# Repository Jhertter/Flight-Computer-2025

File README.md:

# ITBA Rocketry Team - Avionics&recovery
Documentation of SRAD Flight Computer

---

## Description

- Hardware design and implementation of the 2025 on board flight computer.
- Software used to capture data and transmit it to the ground station.

## FC implementation diagram

## Authors

José Ivan Hertter
Ezequiel Diaz Guzmán

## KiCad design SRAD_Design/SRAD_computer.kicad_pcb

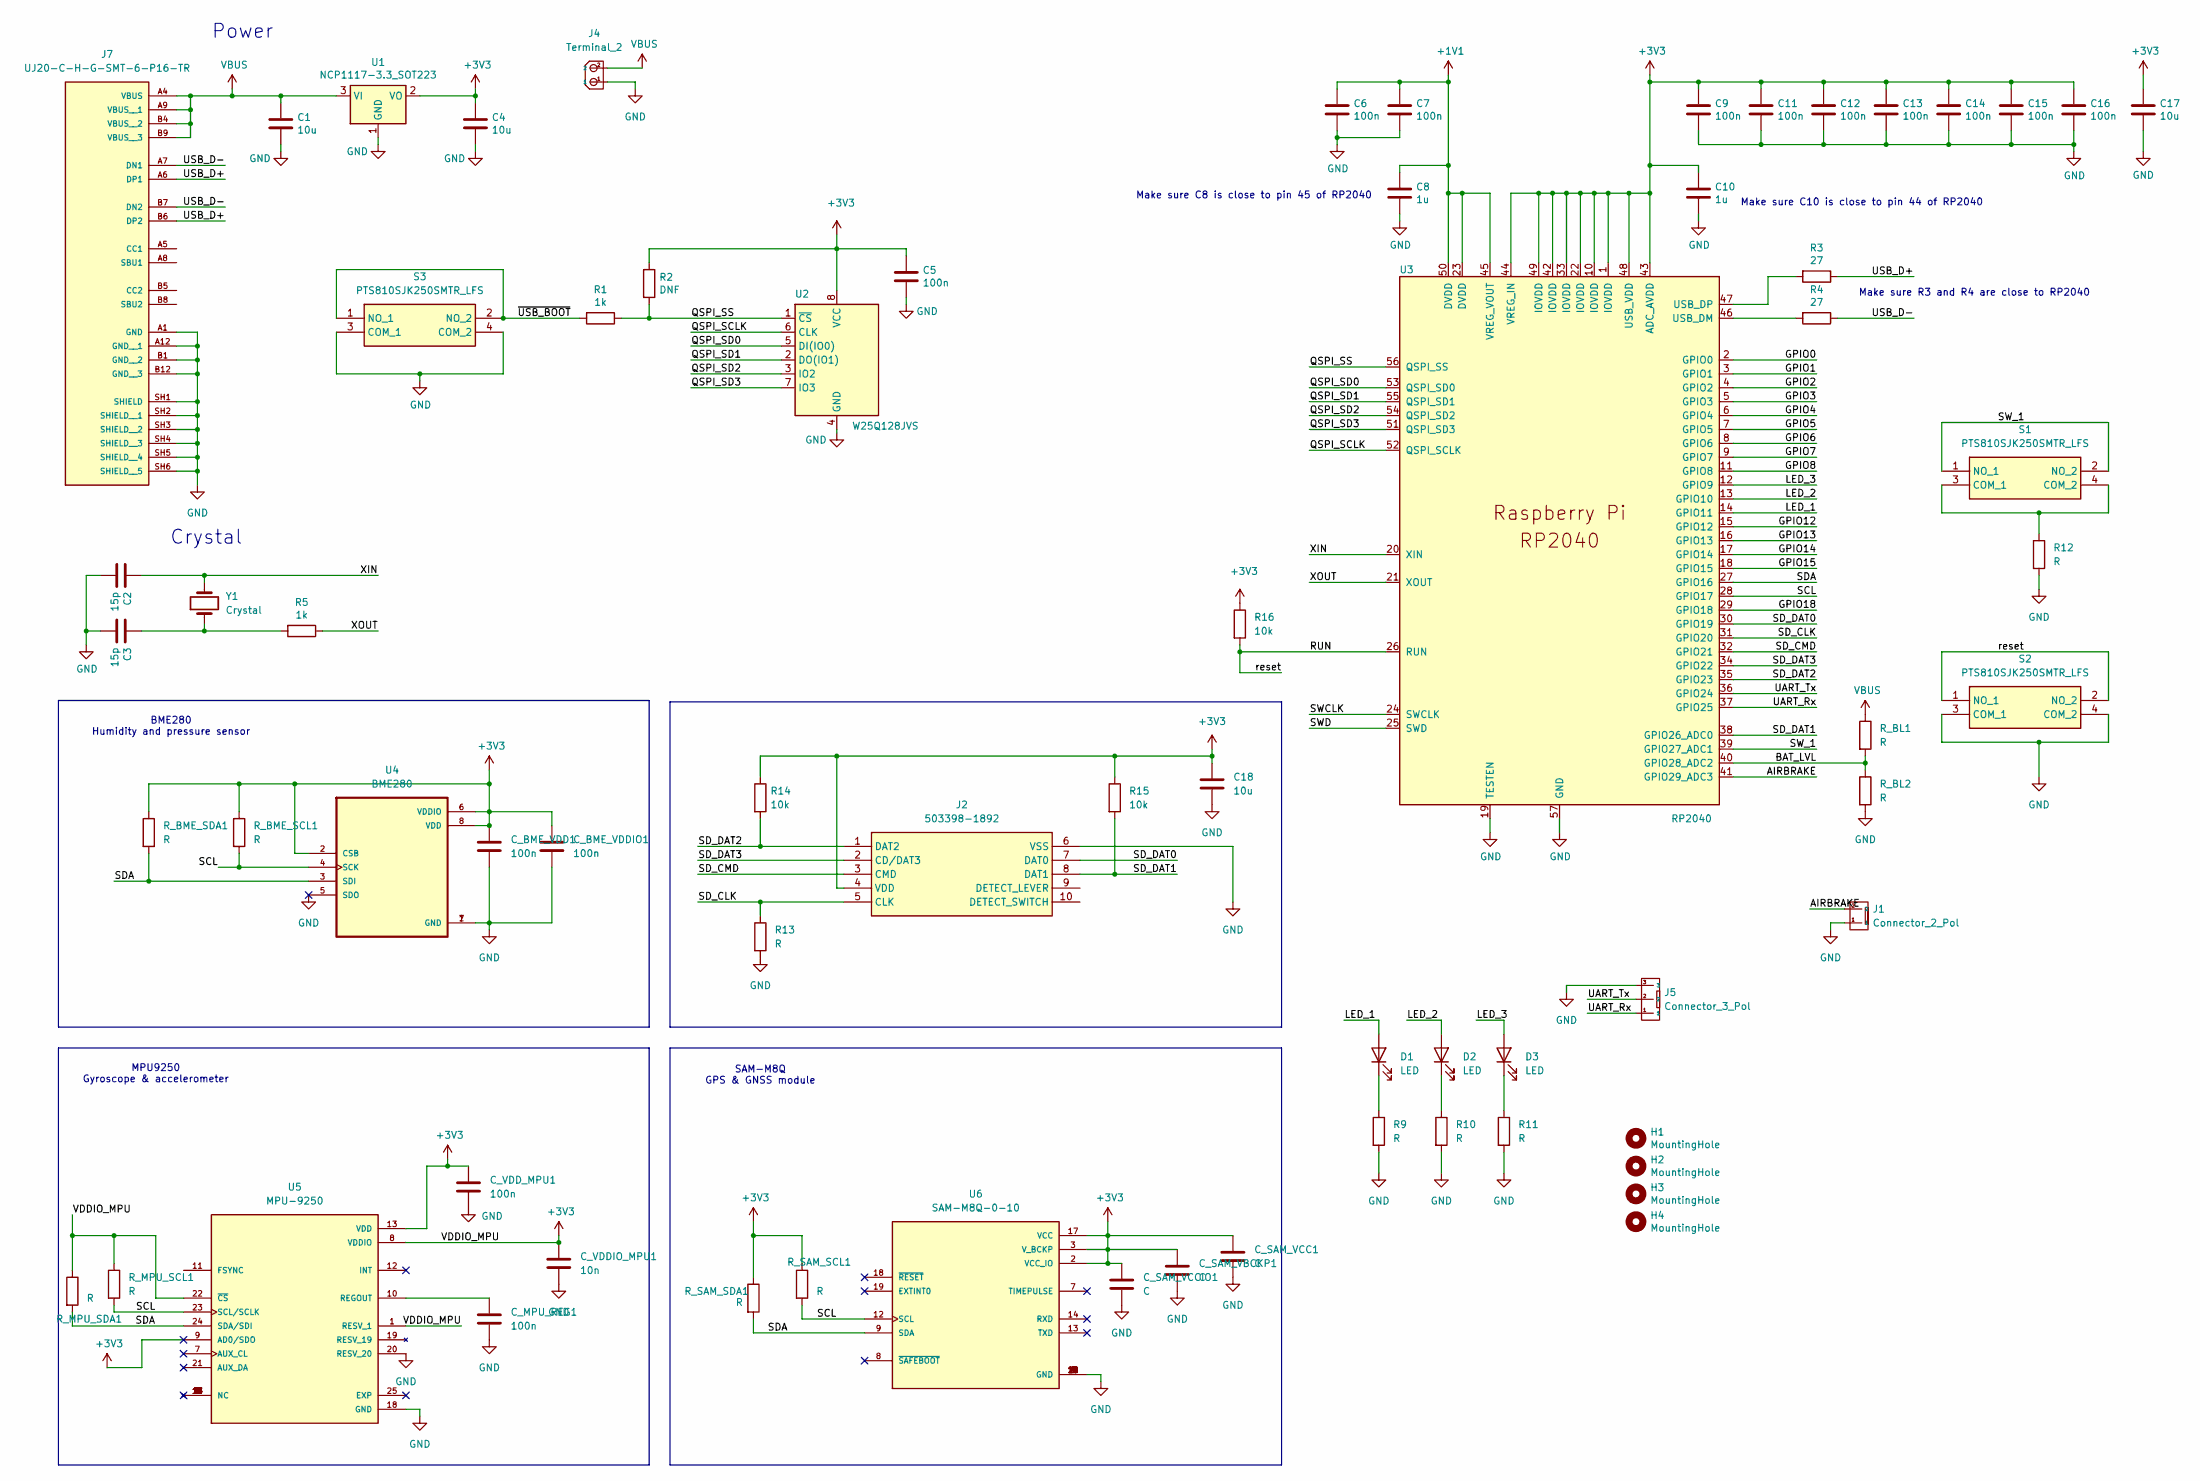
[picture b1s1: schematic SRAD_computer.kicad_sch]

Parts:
C1, C4, C17: 10u; C_0805_2012Metric
C2, C3: 15p; C_0805_2012Metric
C5, C6, C7, C9, C11, C12, C13, C14, C15, C16: 100n; C_0805_2012Metric
C8, C10: 1u; C_0805_2012Metric
C18: 10u; C_0805
C_BME_VDD1: 100n; C_0805
C_BME_VDDIO1: 100n; C_0805
C_MPU_REG1: 100n; C_0805
C_SAM_VBCKP1: C; C_0805
C_SAM_VCC1: C; C_0805
C_SAM_VCCIO1: C; C_0805
C_VDDIO_MPU1: 10n; C_0805
C_VDD_MPU1: 100n; C_0805
D1, D2, D3: LED; LED_0805_2012Metric_Pad1.15x1.40mm_HandSolder
H1, H2, H3, H4: MountingHole; MountingHole_3.5mm
J1: Connector_2_Pol; PinHeader_1x02_P2.54mm_Vertical
J2: 503398-1892; 693071010811; Mouser Part Number 538-503398-1892
J4: Terminal_2; Bornera_2_P5mm
J5: Connector_3_Pol; PinHeader_1x03_P2.54mm_Vertical
J7: UJ20-C-H-G-SMT-6-P16-TR; SAMESKY_UJ20-C-H-G-SMT-6-P16-TR; PARTREV 1.01
R1, R5: 1k; R_0805_2012Metric
R2: DNF; R_0805_2012Metric
R3, R4: 27; R_0805_2012Metric
R9: R; R_0805_2012Metric_Pad1.20x1.40mm_HandSolder
R10, R11, R12, R13: R; R_0805
R14, R15, R16: 10k; R_0805
R_BL1, R_BL2: R; R_0805
R_BME_SCL1: R; R_0805
R_BME_SDA1: R; R_0805
R_MPU_SCL1: R; R_0805
R_MPU_SDA1: R; R_0805
R_SAM_SCL1: R; R_0805
R_SAM_SDA1: R; R_0805
S1, S2, S3: PTS810SJK250SMTR_LFS; PTS810SJK250SMTRLFS; Mouser Part Number 611-PTS810SJK250SMTR
U1: NCP1117-3.3_SOT223; SOT-223-3_TabPin2
U2: W25Q128JVS; SOIC-8_5.3x5.3mm_P1.27mm
U3: RP2040; RP2040-QFN-56
U4: BME280; PSON65P250X250X100-8N
U5: MPU-9250; PARTREV 1.1
U6: SAM-M8Q-0-10; MODULE_SAM-M8Q-0-10; PARTREV R07
Y1: Crystal; Crystal_HC49-4H_Vertical

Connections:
+1V1: C6.1, C7.1, C8.1, U3.23 (DVDD), U3.45 (VREG_VOUT), U3.50 (DVDD)
+3V3: C4.1, C5.1, C9.1, C10.1, C11.1, C12.1, C13.1, C14.1, C15.1, C16.1, C17.1, C18.1, C_BME_VDD1.1, C_BME_VDDIO1.1, C_SAM_VBCKP1.1, C_SAM_VCC1.1, C_SAM_VCCIO1.1, C_VDDIO_MPU1.1, C_VDD_MPU1.1, J2.4 (VDD), R2.1, R14.1, R15.1, R16.1, R_BME_SCL1.1, R_BME_SDA1.1, R_MPU_SCL1.1, R_MPU_SDA1.1, R_SAM_SCL1.1, R_SAM_SDA1.1, U1.2 (VO), U2.8 (VCC), U3.1 (IOVDD), U3.10 (IOVDD), U3.22 (IOVDD), U3.33 (IOVDD), U3.42 (IOVDD), U3.43 (ADC_AVDD), U3.44 (VREG_IN), U3.48 (USB_VDD), U3.49 (IOVDD), U4.2 (CSB), U4.6 (VDDIO), U4.8 (VDD), U5.1 (RESV_1), U5.8 (VDDIO), U5.9 (AD0/SDO), U5.13 (VDD), U5.22 (~CS), U6.2 (VCC_IO), U6.3 (V_BCKP), U6.17 (VCC)
/AIRBRAKE: J1.2, U3.41 (GPIO29_ADC3)
/BAT_LVL: R_BL1.2, R_BL2.1, U3.40 (GPIO28_ADC2)
/GPIO0: U3.2 (GPIO0)
/GPIO1: U3.3 (GPIO1)
/GPIO2: U3.4 (GPIO2)
/GPIO3: U3.5 (GPIO3)
/GPIO4: U3.6 (GPIO4)
/GPIO5: U3.7 (GPIO5)
/GPIO6: U3.8 (GPIO6)
/GPIO7: U3.9 (GPIO7)
/GPIO8: U3.11 (GPIO8)
/GPIO12: U3.15 (GPIO12)
/GPIO13: U3.16 (GPIO13)
/GPIO14: U3.17 (GPIO14)
/GPIO15: U3.18 (GPIO15)
/GPIO18: U3.29 (GPIO18)
/LED_1: D1.2 (A), U3.14 (GPIO11)
/LED_2: D2.2 (A), U3.13 (GPIO10)
/LED_3: D3.2 (A), U3.12 (GPIO9)
/QSPI_SCLK: U2.6 (CLK), U3.52 (QSPI_SCLK)
/QSPI_SD0: U2.5 (DI(IO0)), U3.53 (QSPI_SD0)
/QSPI_SD1: U2.2 (DO(IO1)), U3.55 (QSPI_SD1)
/QSPI_SD2: U2.3 (IO2), U3.54 (QSPI_SD2)
/QSPI_SD3: U2.7 (IO3), U3.51 (QSPI_SD3)
/QSPI_SS: R1.1, R2.2, U2.1 (~CS), U3.56 (QSPI_SS)
/RUN: R16.2, S2.1 (NO_1), S2.2 (NO_2), U3.26 (RUN)
/SCL: R_BME_SCL1.2, R_MPU_SCL1.2, R_SAM_SCL1.2, U3.28 (GPIO17), U4.4 (SCK), U5.23 (SCL/SCLK), U6.12 (SCL)
/SDA: R_BME_SDA1.2, R_MPU_SDA1.2, R_SAM_SDA1.2, U3.27 (GPIO16), U4.3 (SDI), U5.24 (SDA/SDI), U6.9 (SDA)
/SD_CLK: J2.5 (CLK), R13.1, U3.31 (GPIO20)
/SD_CMD: J2.3 (CMD), U3.32 (GPIO21)
/SD_DAT0: J2.7 (DAT0), U3.30 (GPIO19)
/SD_DAT1: J2.8 (DAT1), R15.2, U3.38 (GPIO26_ADC0)
/SD_DAT2: J2.1 (DAT2), R14.2, U3.35 (GPIO23)
/SD_DAT3: J2.2 (CD/DAT3), U3.34 (GPIO22)
/SWCLK: U3.24 (SWCLK)
/SWD: U3.25 (SWD)
/SW_1: S1.1 (NO_1), S1.2 (NO_2), U3.39 (GPIO27_ADC1)
/UART_Rx: J5.1, U3.37 (GPIO25)
/UART_Tx: J5.2, U3.36 (GPIO24)
/USB_D+: J7.A6 (DP1), J7.B6 (DP2), R3.1
/USB_D-: J7.A7 (DN1), J7.B7 (DN2), R4.1
/XIN: C2.1, U3.20 (XIN), Y1.2
/XOUT: R5.1, U3.21 (XOUT)
/~USB_BOOT: R1.2, S3.1 (NO_1), S3.2 (NO_2)
GND: C1.2, C2.2, C3.2, C4.2, C5.2, C6.2, C7.2, C8.2, C9.2, C10.2, C11.2, C12.2, C13.2, C14.2, C15.2, C16.2, C17.2, C18.2, C_BME_VDD1.2, C_BME_VDDIO1.2, C_MPU_REG1.2, C_SAM_VBCKP1.2, C_SAM_VCC1.2, C_SAM_VCCIO1.2, C_VDDIO_MPU1.2, C_VDD_MPU1.2, J1.1, J2.6 (VSS), J4.1, J5.3, J7.A1 (GND), J7.A12 (GND__1), J7.B1 (GND__2), J7.B12 (GND__3), J7.SH1 (SHIELD), J7.SH2 (SHIELD__1), J7.SH3 (SHIELD__2), J7.SH4 (SHIELD__3), J7.SH5 (SHIELD__4), J7.SH6 (SHIELD__5), R9.2, R10.2, R11.2, R12.2, R13.2, R_BL2.2, S2.3 (COM_1), S2.4 (COM_2), S3.3 (COM_1), S3.4 (COM_2), U1.1 (GND), U2.4 (GND), U3.19 (TESTEN), U3.57 (GND), U4.1 (GND), U4.5 (SDO), U4.7 (GND), U5.18 (GND), U5.20 (RESV_20), U6.1 (GND), U6.4 (GND), U6.5 (GND), U6.6 (GND), U6.10 (GND), U6.11 (GND), U6.15 (GND), U6.16 (GND), U6.20 (GND)
unnamed: C3.1, R5.2, Y1.1
unnamed: D1.1 (K), R9.1
unnamed: D2.1 (K), R10.1
unnamed: D3.1 (K), R11.1
unnamed: R12.1, S1.3 (COM_1), S1.4 (COM_2)
unnamed: R4.2, U3.46 (USB_DM)
unnamed: R3.2, U3.47 (USB_DP)
unnamed: C_MPU_REG1.1, U5.10 (REGOUT)
VBUS: C1.1, J4.2, J7.A4 (VBUS), J7.A9 (VBUS__1), J7.B4 (VBUS__2), J7.B9 (VBUS__3), R_BL1.1, U1.3 (VI)

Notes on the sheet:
SAM-M8Q GPS & GNSS module
Crystal
Make sure C10 is close to pin 44 of RP2040
Make sure R3 and R4 are close to RP2040
BME280 Humidity and pressure sensor
MPU9250 Gyroscope & accelerometer
Power
Make sure C8 is close to pin 45 of RP2040

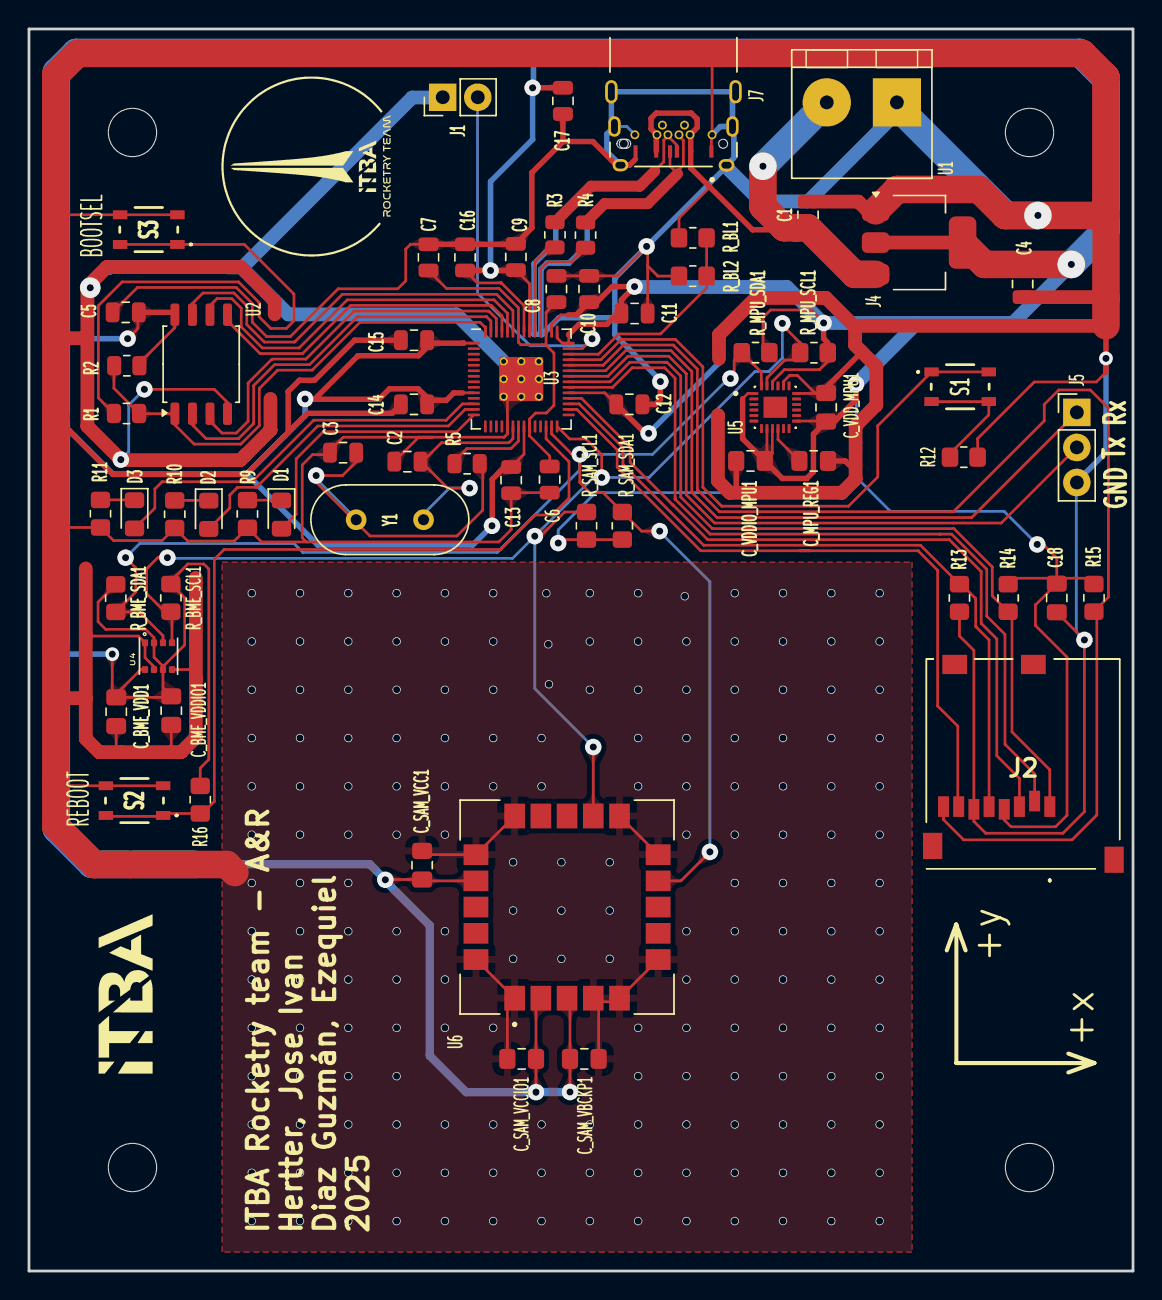
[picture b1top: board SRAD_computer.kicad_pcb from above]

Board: 2 copper layers, 80.0 x 90.0 mm, 69 parts (0 on the bottom side), 40 nets.

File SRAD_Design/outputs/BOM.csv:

"Id";"Designator";"Footprint";"Quantity";"Designation";"Supplier and ref";
1;"D2,D1,D3";"LED_0805_2012Metric_Pad1.15x1.40mm_HandSolder";3;"LED";;;
2;"C_BME_VDDIO1,C_VDD_MPU1,C_MPU_REG1,C_BME_VDD1";"C_0805";4;"100n";;;
3;"C8,C10";"C_0805_2012Metric";2;"1u";;;
4;"R2";"R_0805_2012Metric";1;"DNF";;;
5;"R15,R16,R14";"R_0805";3;"10k";;;
6;"J7";"SAMESKY_UJ20-C-H-G-SMT-6-P16-TR";1;"UJ20-C-H-G-SMT-6-P16-TR";;;
7;"C1,C4,C17";"C_0805_2012Metric";3;"10u";;;
8;"R13,R_BME_SDA1,R_BL2,R_BME_SCL1,R10,R_BL1,R_SAM_SDA1,R_MPU_SCL1,R_MPU_SDA1,R12,R11,R_SAM_SCL1";"R_0805";12;"R";;;
9;"Y1";"Crystal_HC49-4H_Vertical";1;"Crystal";;;
10;"C_VDDIO_MPU1";"C_0805";1;"10n";;;
11;"J5";"PinHeader_1x03_P2.54mm_Vertical";1;"Connector_3_Pol";;;
12;"U1";"SOT-223-3_TabPin2";1;"NCP1117-3.3_SOT223";;;
13;"R3,R4";"R_0805_2012Metric";2;"27";;;
14;"C_SAM_VCCIO1,C_SAM_VCC1,C_SAM_VBCKP1";"C_0805";3;"C";;;
15;"R9";"R_0805_2012Metric_Pad1.20x1.40mm_HandSolder";1;"R";;;
16;"J1";"PinHeader_1x02_P2.54mm_Vertical";1;"Connector_2_Pol";;;
17;"S2,S3,S1";"PTS810SJK250SMTRLFS";3;"PTS810SJK250SMTR_LFS";;;
18;"U2";"SOIC-8_5.3x5.3mm_P1.27mm";1;"W25Q128JVS";;;
19;"C18";"C_0805";1;"10u";;;
20;"C6,C14,C13,C15,C7,C11,C12,C9,C5,C16";"C_0805_2012Metric";10;"100n";;;
21;"U5";"MPU-9250";1;"MPU-9250";;;
22;"R1,R5";"R_0805_2012Metric";2;"1k";;;
23;"J4";"Bornera_2_P5mm";1;"Terminal_2";;;
24;"U4";"PSON65P250X250X100-8N";1;"BME280";;;
25;"C2,C3";"C_0805_2012Metric";2;"15p";;;
26;"U3";"RP2040-QFN-56";1;"RP2040";;;
27;"J2";"693071010811";1;"503398-1892";;;
28;"U6";"MODULE_SAM-M8Q-0-10";1;"SAM-M8Q-0-10";;;

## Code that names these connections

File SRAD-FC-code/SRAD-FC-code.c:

#include <stdio.h>
#include "pico/stdlib.h"
#include "pico/time.h"
// #include "hardware/spi.h"
#include "hardware/i2c.h"
#include "hardware/gpio.h"
#include "hardware/uart.h"
#include "libraries/src/pico-icm20948.h"
#include "libraries/MadgwickAHRS/MadgwickAHRS.h"

#define PIN_LED_COM 11
#define PIN_LED_ALTITUDE 10
#define PIN_LED_0 9

#define PIN_I2C_SDA 16
#define PIN_I2C_SCL 17

#define PIN_UART_TX 26
#define PIN_UART_RX 27

#define PIN_SD_CLK 20
#define PIN_SD_CMD 21
#define PIN_SD_DAT0 19
#define PIN_SD_DAT1 25
#define PIN_SD_DAT2 23
#define PIN_SD_DAT3 22

const static int gpio_size = 3;
const static int gpio_array[] = {
    PIN_LED_COM,
    PIN_LED_ALTITUDE,
    PIN_LED_0};

i2c_inst_t i2c_setUp = {i2c0_hw, false};
icm20948_config_t IMU_config = {0x68, 0x0C, &i2c_setUp};
icm20984_data_t data;
madgwick_ahrs_t filter = {0.5f, {1.0f, 0.0f, 0.0f, 0.0f}};

bool dataflag = false;

bool read_icm20948(repeating_timer_t *rt);
void gpio_toggle(int pin);

int main()
{
    stdio_init_all();

    for (int i = 0; i < gpio_size; i++)
    {
        gpio_init(gpio_array[i]);
        gpio_set_dir(gpio_array[i], GPIO_OUT);
        gpio_put(gpio_array[i], 1);
    }

    i2c_init(&i2c_setUp, 400 * 1000); // 400kHz
    gpio_set_function(PIN_I2C_SDA, GPIO_FUNC_I2C);
    gpio_set_function(PIN_I2C_SCL, GPIO_FUNC_I2C);
    gpio_pull_up(PIN_I2C_SDA);
    gpio_pull_up(PIN_I2C_SCL);

    // Initialize ICM-20948
    sleep_ms(1000);

    uint8_t reg = 0x00;
    uint8_t dat;
    i2c_write_blocking(&i2c_setUp, IMU_config.addr_accel_gyro, &reg, 1, true); // Write register address
    i2c_read_blocking(&i2c_setUp, IMU_config.addr_accel_gyro, &dat, 1, false); // Read response
    printf("WHO_AM_I: 0x%02X\n", dat); // Should return 0xEA for ICM-20948
    gpio_put(PIN_LED_COM, 0);

    if (!icm20948_init(&IMU_config))
        printf("successfully initialized!\n");

    // gpio_put(PIN_LED_ALTITUDE, 0);

    icm20948_cal_gyro(&IMU_config, &data.gyro_bias[0]);
    printf("calibrated gyro: %d %d %d\n", data.gyro_bias[0], data.gyro_bias[1], data.gyro_bias[2]);

    icm20948_cal_accel(&IMU_config, &data.accel_bias[0]);
    printf("calibrated accel: %d %d %d\n", data.accel_bias[0], data.accel_bias[1], data.accel_bias[2]);

    int16_t accel_raw[3] = {0}, gyro_raw[3] = {0}, mag_raw[3] = {0}, temp_raw = 0;
    float accel_g[3] = {0}, gyro_dps[3] = {0}, mag_ut[3] = {0}, temp_c = 0;

    static repeating_timer_t timer;
    add_repeating_timer_ms(-10, &read_icm20948, NULL, &timer);

    
    while (true)
    {
        gpio_toggle(PIN_LED_COM);
        sleep_ms(100);
        gpio_toggle(PIN_LED_ALTITUDE);
        sleep_ms(100);
        gpio_toggle(PIN_LED_0);
        sleep_ms(100);

        if (dataflag)
        {
            dataflag = false;
            // 0: x, 1: y, 2: z
            accel_g[0] = (float)data.accel_raw[0] / 16384.0f;
            accel_g[1] = (float)data.accel_raw[1] / 16384.0f;
            accel_g[2] = (float)data.accel_raw[2] / 16384.0f;
            gyro_dps[0] = (float)data.gyro_raw[0] / 131.0f;
            gyro_dps[1] = (float)data.gyro_raw[1] / 131.0f;
            gyro_dps[2] = (float)data.gyro_raw[2] / 131.0f;
            mag_ut[0] = (float)data.mag_raw[1];
            mag_ut[1] = (float)-data.mag_raw[0];
            mag_ut[2] = (float)-data.mag_raw[2];

            MadgwickAHRSupdate(&filter, gyro_dps[0], gyro_dps[1], gyro_dps[2], accel_g[0] * 9.8, accel_g[1] * 9.8, accel_g[2] * 9.8, mag_ut[0], mag_ut[1], mag_ut[2]);

            // printf("(data->q[0]) %0.1f, (data->q[1]) %0.1f, (data->q[2]) %0.1f, (data->q[3]) %0.1f\n", (data->q[0]), (data->q[1]), (data->q[2]), (data->q[3]));
            // printf("Roll %0.1f, Pitch %0.1f, Yaw %0.1f\n", euler[0] * 57.29578f, euler[1] * 57.29578f, euler[2] * 57.29578f + 180.0f);

            // accel(g)   = raw_value / (65535 / full_scale)
            // ex) if full_scale == +-4g then accel = raw_value / (65535 / 8) = raw_value / 8192
            // gyro(dps)  = raw_value / (65535 / full_scale)
            // ex) if full_scale == +-250dps then gyro = raw_value / (65535 / 500) = raw_value / 131
            // mag(uT)    = raw_value / (32752 / 4912) = (approx) raw_value / 20 * 3
            printf("accel. x: %+2.5f, y: %+2.5f, z:%+2.5f\n", accel_g[0], accel_g[1], accel_g[2]);
            printf("gyro.  x: %+2.5f, y: %+2.5f, z:%+2.5f\n", gyro_dps[0], gyro_dps[1], gyro_dps[2]);
            printf("mag.   x: %+2.5f, y: %+2.5f, z:%+2.5f\n", mag_ut[0], mag_ut[1], mag_ut[2]);
            // printf("temp: %+2.5f\n", data.temp_c);
        }
    }
}

void gpio_toggle(int pin)
{
    if (gpio_get(pin))
        gpio_put(pin, 0);
    else
        gpio_put(pin, 1);
}

bool read_icm20948(repeating_timer_t *rt)
{
    icm20948_read_cal_accel(&IMU_config, &data.accel_raw[0], &data.accel_bias[0]);
    icm20948_read_cal_gyro(&IMU_config, &data.gyro_raw[0], &data.gyro_bias[0]);
    icm20948_read_cal_mag(&IMU_config, &data.mag_raw[0], &data.mag_bias[0]);
    icm20948_read_temp_c(&IMU_config, &data.temp_c);
    dataflag = true;
    return true;
}

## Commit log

2025-01-21 datasheet and minimal hardware design
2025-03-11 creación proyecto kicad
2025-03-11 RP2040 minimal components placed
2025-03-17 schematic update: MPU, BME & SAM m8q
2025-03-18 PCB placement
2025-03-19 RP2040 decoupling capacitors and resistances connection
2025-03-21 update PCB
2025-03-21 PCB Update
2025-03-27 Change Layout: Shield for GPS
2025-03-27 Changed board size & GPS shielding
2025-03-28 Update PCB placement & 3D models added
2025-03-28 PCB v1
2025-03-31 SD slot, LEDs and switch added
2025-04-01 PCB_V1 finished
2025-04-01 PCB 3D model added
2025-04-03 Creación proyecto rp2040
2025-04-04 PCB V2 first draft
2025-04-06 changes in USB pins. D+ -> D-
2025-04-06 USB gnd fixed
2025-04-07 SD layout
2025-04-08 USB footprint changed & reboot sw added
2025-04-08 GPS ground plane fixed
2025-04-09 reboot and bootsel buttons added
2025-04-09 test code
2025-04-09 icm libraries added
2025-04-09 Reading data from IMU: Done
2025-04-10 Work in progress: migrate arduino libraries to rpi
2025-04-10 Migration finished
2025-04-11 Migration Failed - Reimagining M8Q driver
2025-04-11 Pin for battery level added
2025-04-12 Restoring m8q library
2025-04-14 m8q does not respond - ERROR 404
2025-04-14 M8Q version 2
2025-04-14 Gerber files added
2025-04-14 changed SD socket & updated gerber files
2025-04-14 Better 3D model created
2025-04-14 Rearranged some files
2025-04-14 Changed micro SD socket footprint
2025-05-01 ublox library changes
2025-05-01 added bme libraries: still under test
2025-05-02 XBee class added: parser in progress & mission time; ESU driver added: not working
2025-05-05 camilasalvadora
2025-05-05 Prueba en ITBA
2025-05-06 ram (?)
2025-05-06 reorganized directory
2025-05-09 XBee parser updated: parses 1 pararam, not whole message. Function to save data to flash
2025-05-09 XBee class tested with xbee module -> passed
2025-05-09 flash changes
2025-05-11 saveData function now contemplates "out of memory" condition
2025-05-12 readData from flash
2025-05-12 IMU fixed
2025-05-12 minor changes
2025-05-12 paser accepts negative numbers
2025-05-13 XBee: pitch & roll work fine; Still troubleshooting velocity
2025-05-13 Updated PCB: some UART pin errors & missing conection on icm
2025-05-13 velocity testing: firsts approach
2025-05-14 ZUPT: simple zero velocity update algorithm added to mitigate velofity drift
2025-05-14 FSM first draft
2025-05-14 XBee class reorganized
2025-05-14 main updated -> already on main
2025-05-15 README update
2025-05-18 transmission test completed
2025-05-21 fsm update: test features added
2025-05-21 dummy commit: Para sulli
2025-05-22 Serial plotter
2025-05-22 issue setting navigation rate: sendCommand does not ACK
2025-05-22 SAM M8Q library bug found, ready for testing
2025-05-22 GNSS transmission rate fixed
2025-05-23 Velocity testbench: extracted data from past editions
2025-05-23 FSM was replaced with a simpler version
2025-05-23 Airbrake function
2025-05-23 Save global parameters function implemented. Savedata implemented
2025-05-24 v1 SRAD computer finished: test remaining
2025-05-30 Pre test
2025-05-30 parser error & bme altitude fixed; test bench data ready
2025-05-30 uart_getc problem
2025-06-01 STARUP SIGNAl working
2025-06-04 fsm tested
2025-06-09 Send telemetry while PRE_LAUNCH; APOGEE routine updated; airbrake on from AIRBRAKE_HEIGHT to real max height
2025-06-10 LED_ON turns on on ASCENT
2025-06-10 bug fix
2025-06-10 xbee buf fix: to be revised
2025-06-11 Comentado de guardados globales en la flash. Los guardados frecuentes se siguen haciendo
